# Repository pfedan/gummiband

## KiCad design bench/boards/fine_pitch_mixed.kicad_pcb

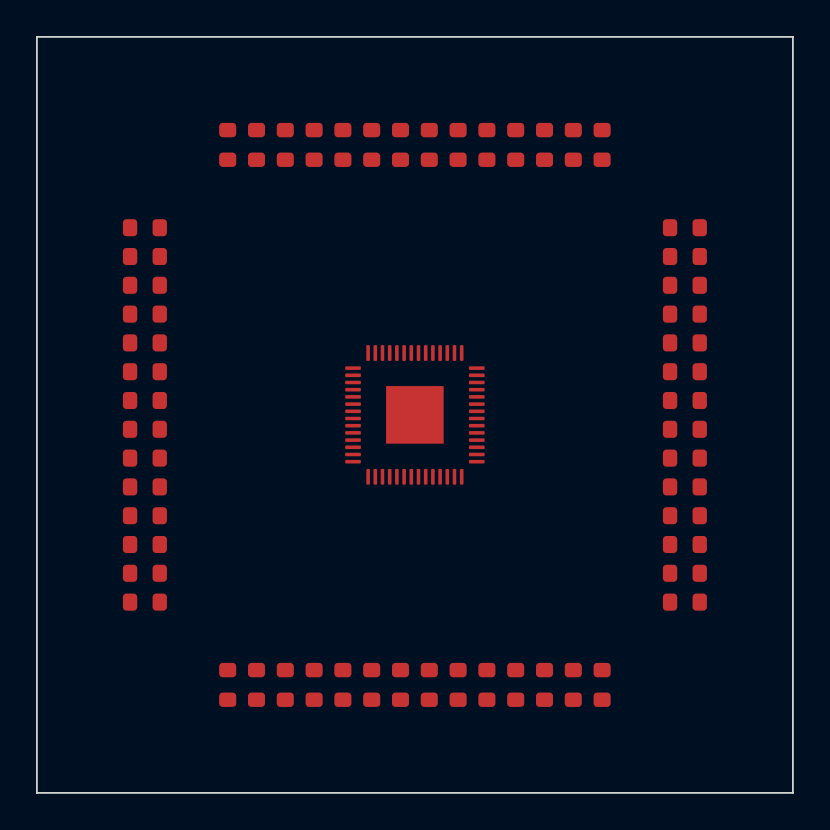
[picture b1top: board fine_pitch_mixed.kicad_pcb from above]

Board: 2 copper layers, 42.0 x 42.0 mm, 57 parts (0 on the bottom side), 57 nets, no tracks yet.

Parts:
R1, R2, R3, R4, R5, R6, R7, R8, R9, R10, R11, R12, R13, R14, R15, R16, R17, R18, R19, R20, R21, R22, R23, R24, R25, R26, R27, R28, R29, R30, R31, R32, R33, R34, R35, R36, R37, R38, R39, R40, R41, R42, R43, R44, R45, R46, R47, R48, R49, R50, R51, R52, R53, R54, R55, R56: 10k; R_0603
U1: MCU; QFN-56

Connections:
F1: R1.1, U1.32
F2: R2.1, U1.12
F3: R3.1, U1.23
F4: R4.1, U1.54
F5: R5.1, U1.10
F6: R6.1, U1.16
F7: R7.1, U1.33
F8: R8.1, U1.28
F9: R9.1, U1.21
F10: R10.1, U1.56
F11: R11.1, U1.19
F12: R12.1, U1.26
F13: R13.1, U1.43
F14: R14.1, U1.11
F15: R15.1, U1.51
F16: R16.1, U1.41
F17: R17.1, U1.3
F18: R18.1, U1.53
F19: R19.1, U1.29
F20: R20.1, U1.48
F21: R21.1, U1.47
F22: R22.1, U1.44
F23: R23.1, U1.18
F24: R24.1, U1.45
F25: R25.1, U1.50
F26: R26.1, U1.49
F27: R27.1, U1.6
F28: R28.1, U1.8
F29: R29.1, U1.13
F30: R30.1, U1.52
F31: R31.1, U1.30
F32: R32.1, U1.39
F33: R33.1, U1.25
F34: R34.1, U1.9
F35: R35.1, U1.4
F36: R36.1, U1.38
F37: R37.1, U1.2
F38: R38.1, U1.14
F39: R39.1, U1.37
F40: R40.1, U1.17
F41: R41.1, U1.22
F42: R42.1, U1.5
F43: R43.1, U1.40
F44: R44.1, U1.24
F45: R45.1, U1.7
F46: R46.1, U1.15
F47: R47.1, U1.46
F48: R48.1, U1.27
F49: R49.1, U1.35
F50: R50.1, U1.20
F51: R51.1, U1.34
F52: R52.1, U1.42
F53: R53.1, U1.31
F54: R54.1, U1.1
F55: R55.1, U1.36
F56: R56.1, U1.55
GND: R1.2, R2.2, R3.2, R4.2, R5.2, R6.2, R7.2, R8.2, R9.2, R10.2, R11.2, R12.2, R13.2, R14.2, R15.2, R16.2, R17.2, R18.2, R19.2, R20.2, R21.2, R22.2, R23.2, R24.2, R25.2, R26.2, R27.2, R28.2, R29.2, R30.2, R31.2, R32.2, R33.2, R34.2, R35.2, R36.2, R37.2, R38.2, R39.2, R40.2, R41.2, R42.2, R43.2, R44.2, R45.2, R46.2, R47.2, R48.2, R49.2, R50.2, R51.2, R52.2, R53.2, R54.2, R55.2, R56.2, U1.57

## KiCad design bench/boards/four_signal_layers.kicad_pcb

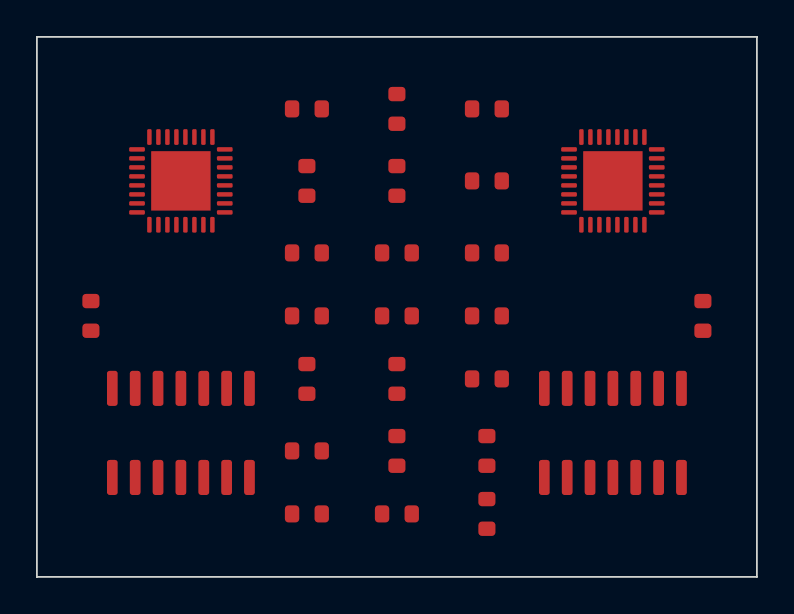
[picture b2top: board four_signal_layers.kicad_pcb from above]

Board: 4 copper layers, 40.0 x 30.0 mm, 27 parts (0 on the bottom side), 53 nets, no tracks yet.

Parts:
C4, C8, C12, C16, C20: 10k; C_0603
R1, R2, R3, R5, R6, R7, R9, R10, R11, R13, R14, R15, R17, R18, R19, R21, R22, R23: 10k; R_0603
U1, U2: MCU; QFN-32
U3, U4: IC; SOIC-14

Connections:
GND: C4.2, C8.2, C12.2, C16.2, C20.2, U1.33, U2.33
N1: R7.1, R22.2, U1.14, U3.11
N2: R3.2, R23.1, U2.13
N3: R1.1, U1.24
N4: U2.20, U4.8
N5: R9.2, U4.14
N6: R13.2, U1.11, U1.13, U3.12
N7: R2.1, U2.3
N8: C12.1, R6.2, U2.27
N9: R3.1, U2.19
N10: C16.1, R19.2, U3.9
N11: R2.2, U1.31
N12: C4.1, U1.28
N13: C8.1, U1.17
N14: R5.1, U2.32
N15: R10.1, R14.2, U3.4
N16: R9.1, U2.15, U4.11
N17: R13.1, U3.8
N18: R18.1, U4.13
N19: R6.1, U2.31
N20: R5.2, R11.1, U2.1
N21: R18.2, U2.16, U4.6
N22: R21.1, U4.5
N23: U1.20, U3.13
N24: R14.1, R21.2
N25: R22.1, U1.7, U1.12, U3.10
N26: R11.2, U1.29, U3.3, U3.5
N27: R15.1, R17.2, U4.4
N28: R7.2, R10.2, U1.5, U3.6
N29: U1.27, U3.1, U3.7
N30: U1.10, U2.8, U3.2, U3.14
N31: U2.9, U4.1, U4.2
N32: R23.2, U2.30, U4.9
N33: R15.2, U4.10
N34: U1.3, U2.10
N35: R19.1, U1.2
N36: R17.1, U1.22, U2.7
N37: R1.2, U1.8, U2.5
N38: U1.16, U2.28
N39: U1.25, U2.17
N40: U1.18, U2.14, U4.12
N41: U1.15, U2.6
N42: U1.4, U2.22
N43: U1.30, U2.25
N44: U1.9, U2.2, U2.12
N45: U1.26, U2.24
N46: U1.19, U4.3
N47: U2.23, U4.7
N48: U1.6, U2.21
N49: U1.21, U2.4
N50: C20.1, U1.1, U2.26
N51: U1.32, U2.29
N52: U1.23, U2.11, U2.18

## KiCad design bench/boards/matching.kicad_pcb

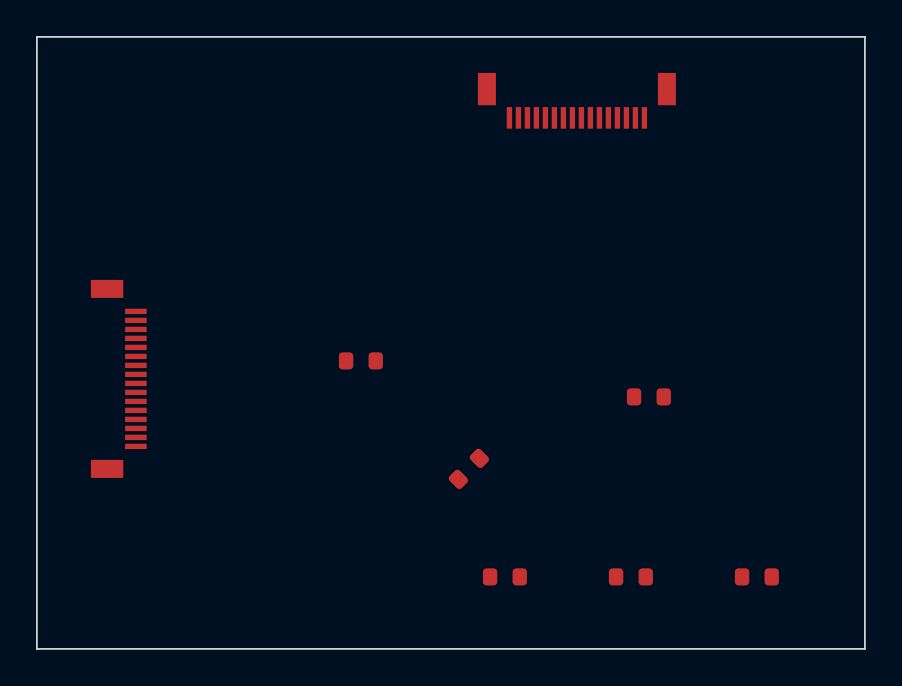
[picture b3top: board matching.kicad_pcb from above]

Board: 2 copper layers, 46.0 x 34.0 mm, 8 parts (0 on the bottom side), 18 nets, no tracks yet.

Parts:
C1, C2, C3, C4, C5, C6: 100n; C_0603
J1, J2: FPC; FPC-16P-0.5mm

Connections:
CLK_N: J1.3, J2.14
CLK_P: J1.4, J2.13
DQ0: J1.15, J2.2
DQ1: J1.14, J2.3
DQ2: J1.13, J2.4
DQ3: J1.12, J2.5
DQ4: J1.9, J2.8
DQ5: J1.8, J2.9
DQ6: J1.7, J2.10
DQ7: J1.6, J2.11
DQS_N: J1.10, J2.7
DQS_P: J1.11, J2.6
G1: J1.5, J2.12
G2: J1.2, J2.15
GND: C1.1, C2.1, C3.1, C4.1, C5.1, C6.1, J1.1, J1.16, J2.1, J2.16
V1: C1.2, C4.2
V2: C2.2, C5.2
V3: C3.2, C6.2

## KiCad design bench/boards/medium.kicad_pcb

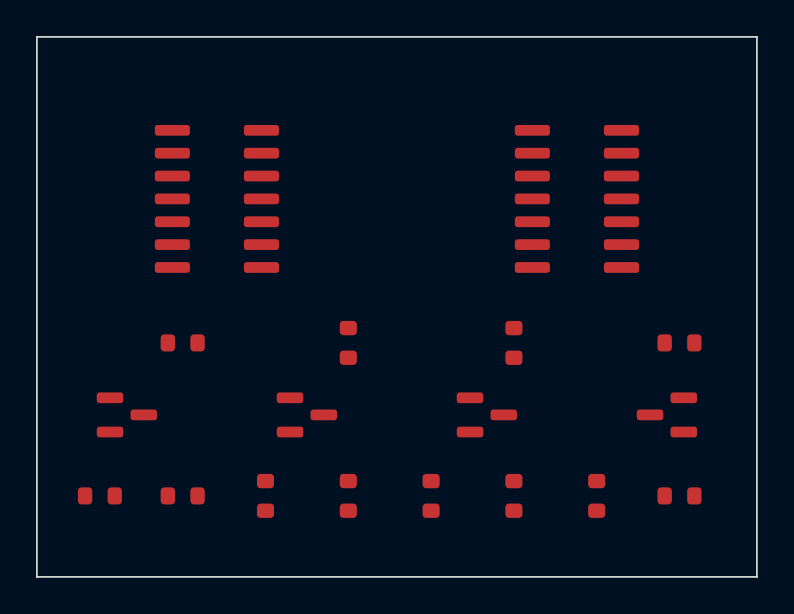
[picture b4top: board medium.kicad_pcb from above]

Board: 2 copper layers, 40.0 x 30.0 mm, 18 parts (0 on the bottom side), 22 nets, no tracks yet.

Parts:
C3, C6, C9, C12: 10k; C_0603
Q1, Q2, Q3, Q4: Q; SOT-23
R1, R2, R4, R5, R7, R8, R10, R11: 10k; R_0603
U1, U2: IC; SOIC-14

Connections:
GND: C3.2, C6.2, C9.2, C12.2, U1.7, U2.7
N1: R1.2, U1.3
N2: Q1.1, Q1.3, U1.1
N3: Q4.1, R4.2
N4: Q1.2, R2.1, R2.2, U1.4
N5: Q2.1, Q2.2, Q2.3, U1.8
N6: Q3.1, U2.1
N7: R7.2, U1.5
N8: C9.1, Q3.2, R7.1, R8.2
N9: R1.1, U1.11
N10: Q3.3, R10.2, R11.1
N11: C3.1, R4.1, U2.10
N12: Q4.3, R11.2, U2.8
N13: U1.10, U2.5
N14: R5.2, U1.9
N15: Q4.2, R10.1, U1.12, U2.4
N16: U1.13, U2.11
N17: U1.14, U2.2
N18: C6.1, U1.6
N19: R5.1, R8.1
N20: C12.1, U2.6
N21: U1.2, U2.14

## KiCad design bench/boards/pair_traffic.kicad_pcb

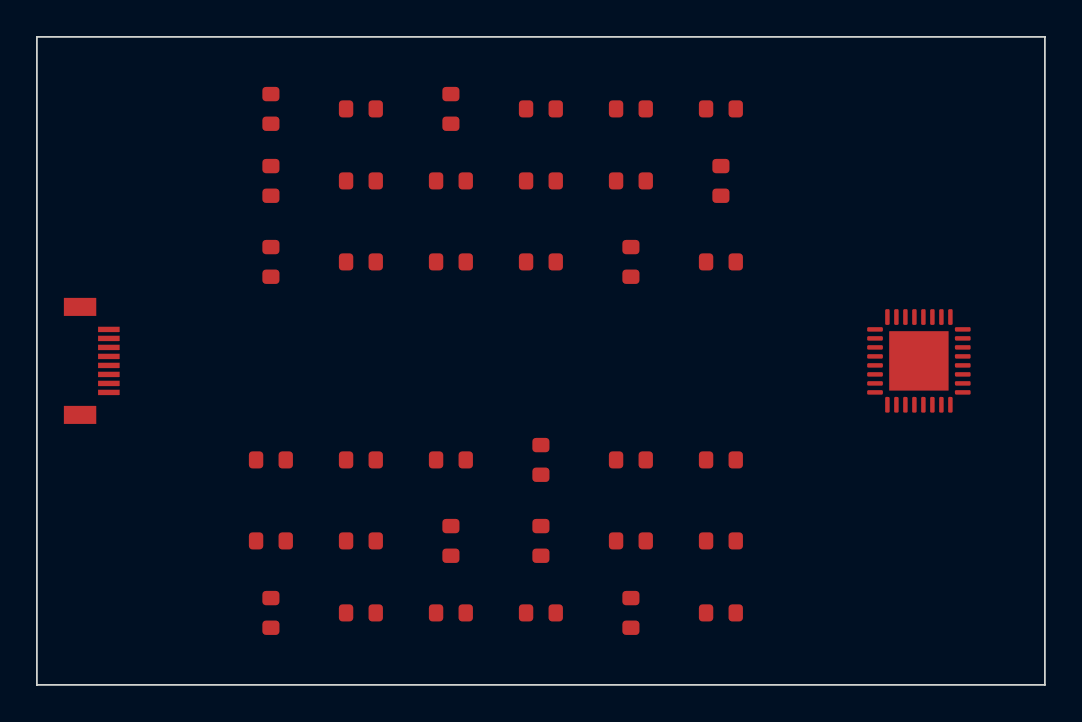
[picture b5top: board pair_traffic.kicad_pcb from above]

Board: 2 copper layers, 56.0 x 36.0 mm, 38 parts (0 on the bottom side), 35 nets, no tracks yet.

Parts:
J1: FPC; FPC-8P-0.5mm
R1, R2, R3, R4, R5, R6, R7, R8, R9, R10, R11, R12, R13, R14, R15, R16, R17, R18, R19, R20, R21, R22, R23, R24, R25, R26, R27, R28, R29, R30, R31, R32, R33, R34, R35, R36: 10k; R_0603
U1: MCU; QFN-32

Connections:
LVDS_N: J1.2, U1.7
LVDS_P: J1.3, U1.6
N1: R11.2, R12.2, R18.1
N2: R3.1, R4.1
N3: R3.2, R9.1, R15.2
N4: R26.2, R32.1
N5: R7.2, R13.2
N6: R28.2, R34.2
N7: R2.2, R8.1
N8: R10.2, R16.1
N9: R19.2, R25.2
N10: R21.2, R22.2
N11: R1.1, R2.1, R14.1
N12: R33.1, R34.1
N13: R27.2, R33.2
N14: R8.2, R9.2, R16.2
N15: R1.2, R7.1
N16: R23.1, R24.2
N17: R22.1, R23.2, R30.1
N18: R13.1, R14.2, R20.1
N19: R30.2, R35.1, R36.2
N20: R17.1, R18.2
N21: R19.1, R25.1, R31.2
N22: R20.2, R27.1
N23: R6.1, R12.1
N24: R4.2, R11.1
N25: R21.1, R29.2
N26: R5.2, R10.1
N27: R29.1, R35.2
N28: R15.1, R24.1
N29: R6.2, R17.2, R28.1
N30: R31.1, R36.1
N31: R5.1, R26.1, R32.2
USB_N: J1.6, U1.3
USB_P: J1.7, U1.2

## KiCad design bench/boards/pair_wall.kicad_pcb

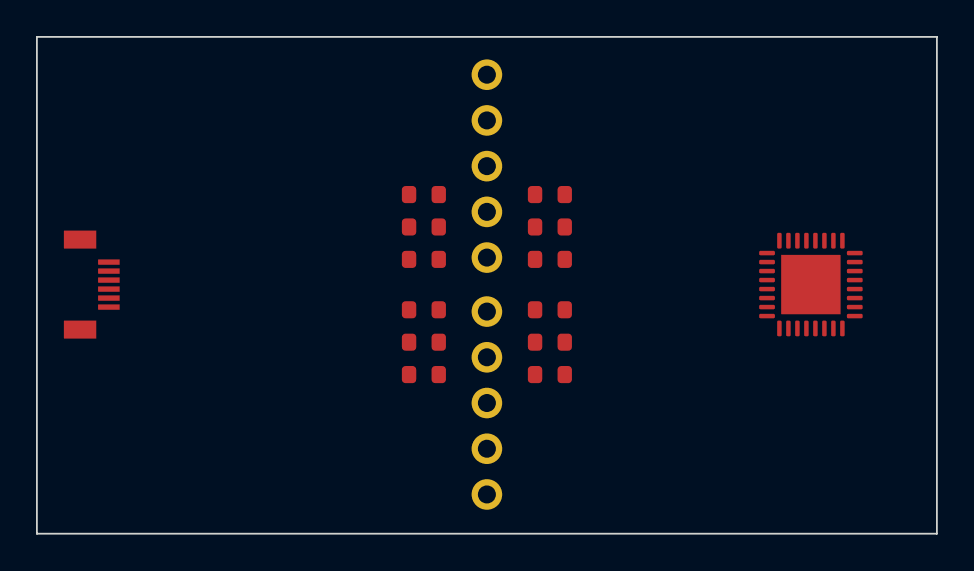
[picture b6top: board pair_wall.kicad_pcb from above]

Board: 2 copper layers, 50.0 x 27.6 mm, 15 parts (0 on the bottom side), 8 nets, no tracks yet.

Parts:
J1: FPC; FPC-6P-0.5mm
R1, R2, R3, R4, R5, R6, R7, R8, R9, R10, R11, R12: 10k; R_0603
U1: MCU; QFN-32
W1: NC; Wall_10

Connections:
S1: R1.2, R7.1
S2: R2.2, R8.1
S3: R3.2, R9.1
S4: R4.2, R10.1
S5: R5.2, R11.1
S6: R6.2, R12.1
USB_N: J1.3, U1.5
USB_P: J1.4, U1.4

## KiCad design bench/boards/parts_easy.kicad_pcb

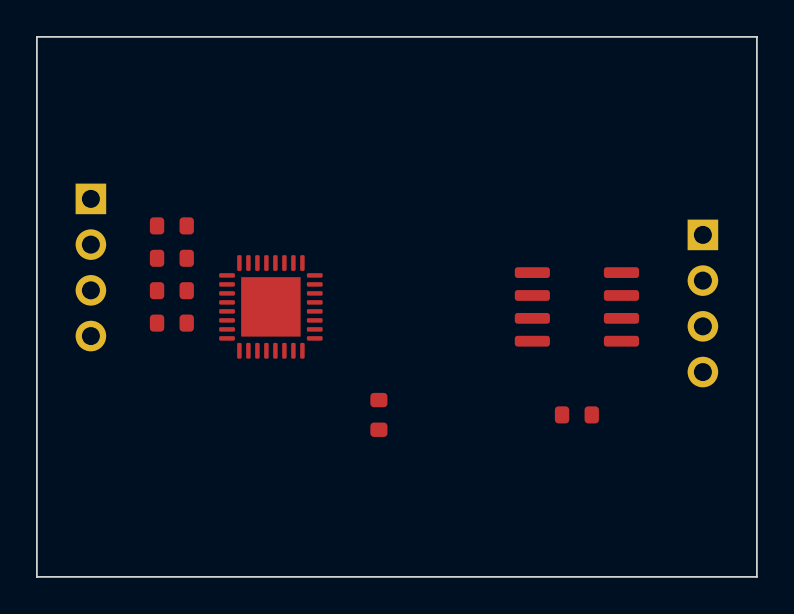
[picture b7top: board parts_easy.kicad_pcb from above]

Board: 2 copper layers, 40.0 x 30.0 mm, 10 parts (0 on the bottom side), 16 nets, no tracks yet.

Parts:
C1, C2: 100n; C_0603
J1, J2: Conn; PinHeader_1x04
R1, R2, R3, R4: 10k; R_0603
U1: MCU; QFN-32
U2: Flash; SOIC-8

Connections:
+3V3: C1.1, C2.1, J2.3, U1.17, U2.8
CS: U1.22, U2.1
GND: C1.2, C2.2, J2.4, U1.33, U2.5
H1: J1.1, R1.1
H2: J1.2, R2.1
H3: J1.3, R3.1
H4: J1.4, R4.1
HOLD: J2.2, U2.7
L1: R1.2, U1.2
L2: R2.2, U1.4
L3: R3.2, U1.6
L4: R4.2, U1.8
MISO: U1.21, U2.2
MOSI: U1.20, U2.3
SCK: U1.19, U2.4
WP: J2.1, U2.6

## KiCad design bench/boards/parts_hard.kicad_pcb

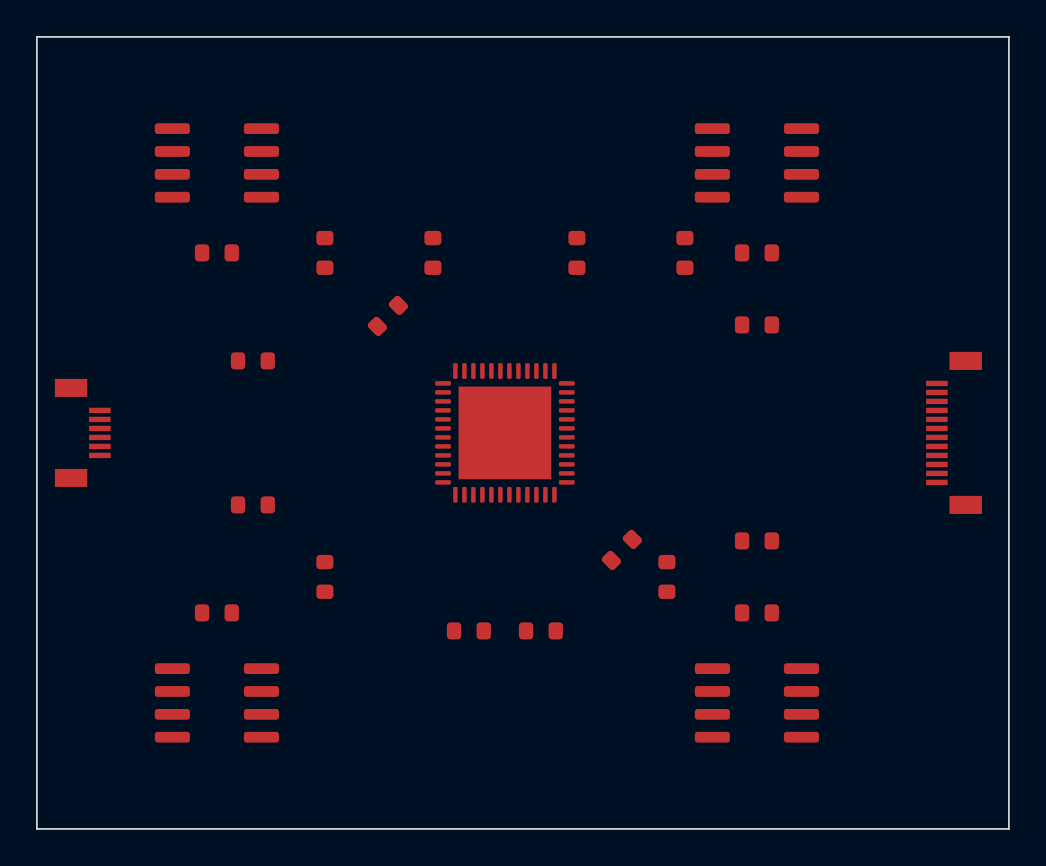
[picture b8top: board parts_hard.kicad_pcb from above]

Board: 2 copper layers, 54.0 x 44.0 mm, 25 parts (0 on the bottom side), 37 nets, no tracks yet.

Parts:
C1, C2, C3, C4, C5, C6: 100n; C_0603
J1: FPC; FPC-12P-0.5mm
J2: FPC; FPC-6P-0.5mm
R1, R2: 4k7; R_0603
R3, R4, R5, R6, R7, R8, R9, R10, R11, R12: 10k; R_0603
U1: MCU; QFN-48
U2: Flash; SOIC-8
U3: ADC; SOIC-8
U4: Sensor; SOIC-8
U5: EEPROM; SOIC-8

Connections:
+3V3: C1.1, C2.1, C3.1, C4.1, C5.1, C6.1, J1.2, J1.11, R1.1, R2.1, U1.6, U2.8, U3.8, U4.8, U5.8
CS0: U1.46, U2.1
CS1: U1.39, U3.1
D0: J1.3, U1.34
D1: J1.5, U1.32
D2: J1.4, U1.33
D3: J1.6, U1.31
D4: J1.7, U1.30
D5: J1.9, U1.28
D6: J1.8, U1.29
D7: J1.10, U1.27
GND: C1.2, C2.2, C3.2, C4.2, C5.2, C6.2, J1.1, J1.12, J2.1, J2.6, U1.7, U1.49, U2.4, U3.4, U4.4, U5.4
INT0: U1.15, U4.1
MISO: U1.44, U2.2, U3.2
MOSI: U1.42, U2.5, U3.5
N1: R7.2, R10.2, U1.14
N2: R4.1, U1.45
N3: R12.1, U1.25
N4: R5.1, R7.1, U1.22
N5: R5.2, U1.36
N6: R3.1, U1.3
N7: R6.2, U1.38
N8: R4.2, R10.1, U1.8
N9: R9.2, U1.4
N10: R3.2, U1.13
N11: R8.2, U1.26
N12: R8.1, U1.47
N13: R12.2, U1.11
N14: R6.1, R11.1, U1.37
N15: R11.2, U1.40
N16: R9.1, U1.5
SCK: U1.43, U2.6, U3.6
SCL: R2.2, U1.18, U4.6, U5.6
SDA: R1.2, U1.17, U4.5, U5.5
USB_N: J2.3, U1.10
USB_P: J2.4, U1.9
WC: U1.21, U5.1
